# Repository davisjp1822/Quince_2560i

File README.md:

# Quince_2560i
Digital Input Protection Board with Ethernet for the Arduino Mega 2560

More information (and board available for purchase) at [https://www.three-ml.com](https://www.three-ml.com)

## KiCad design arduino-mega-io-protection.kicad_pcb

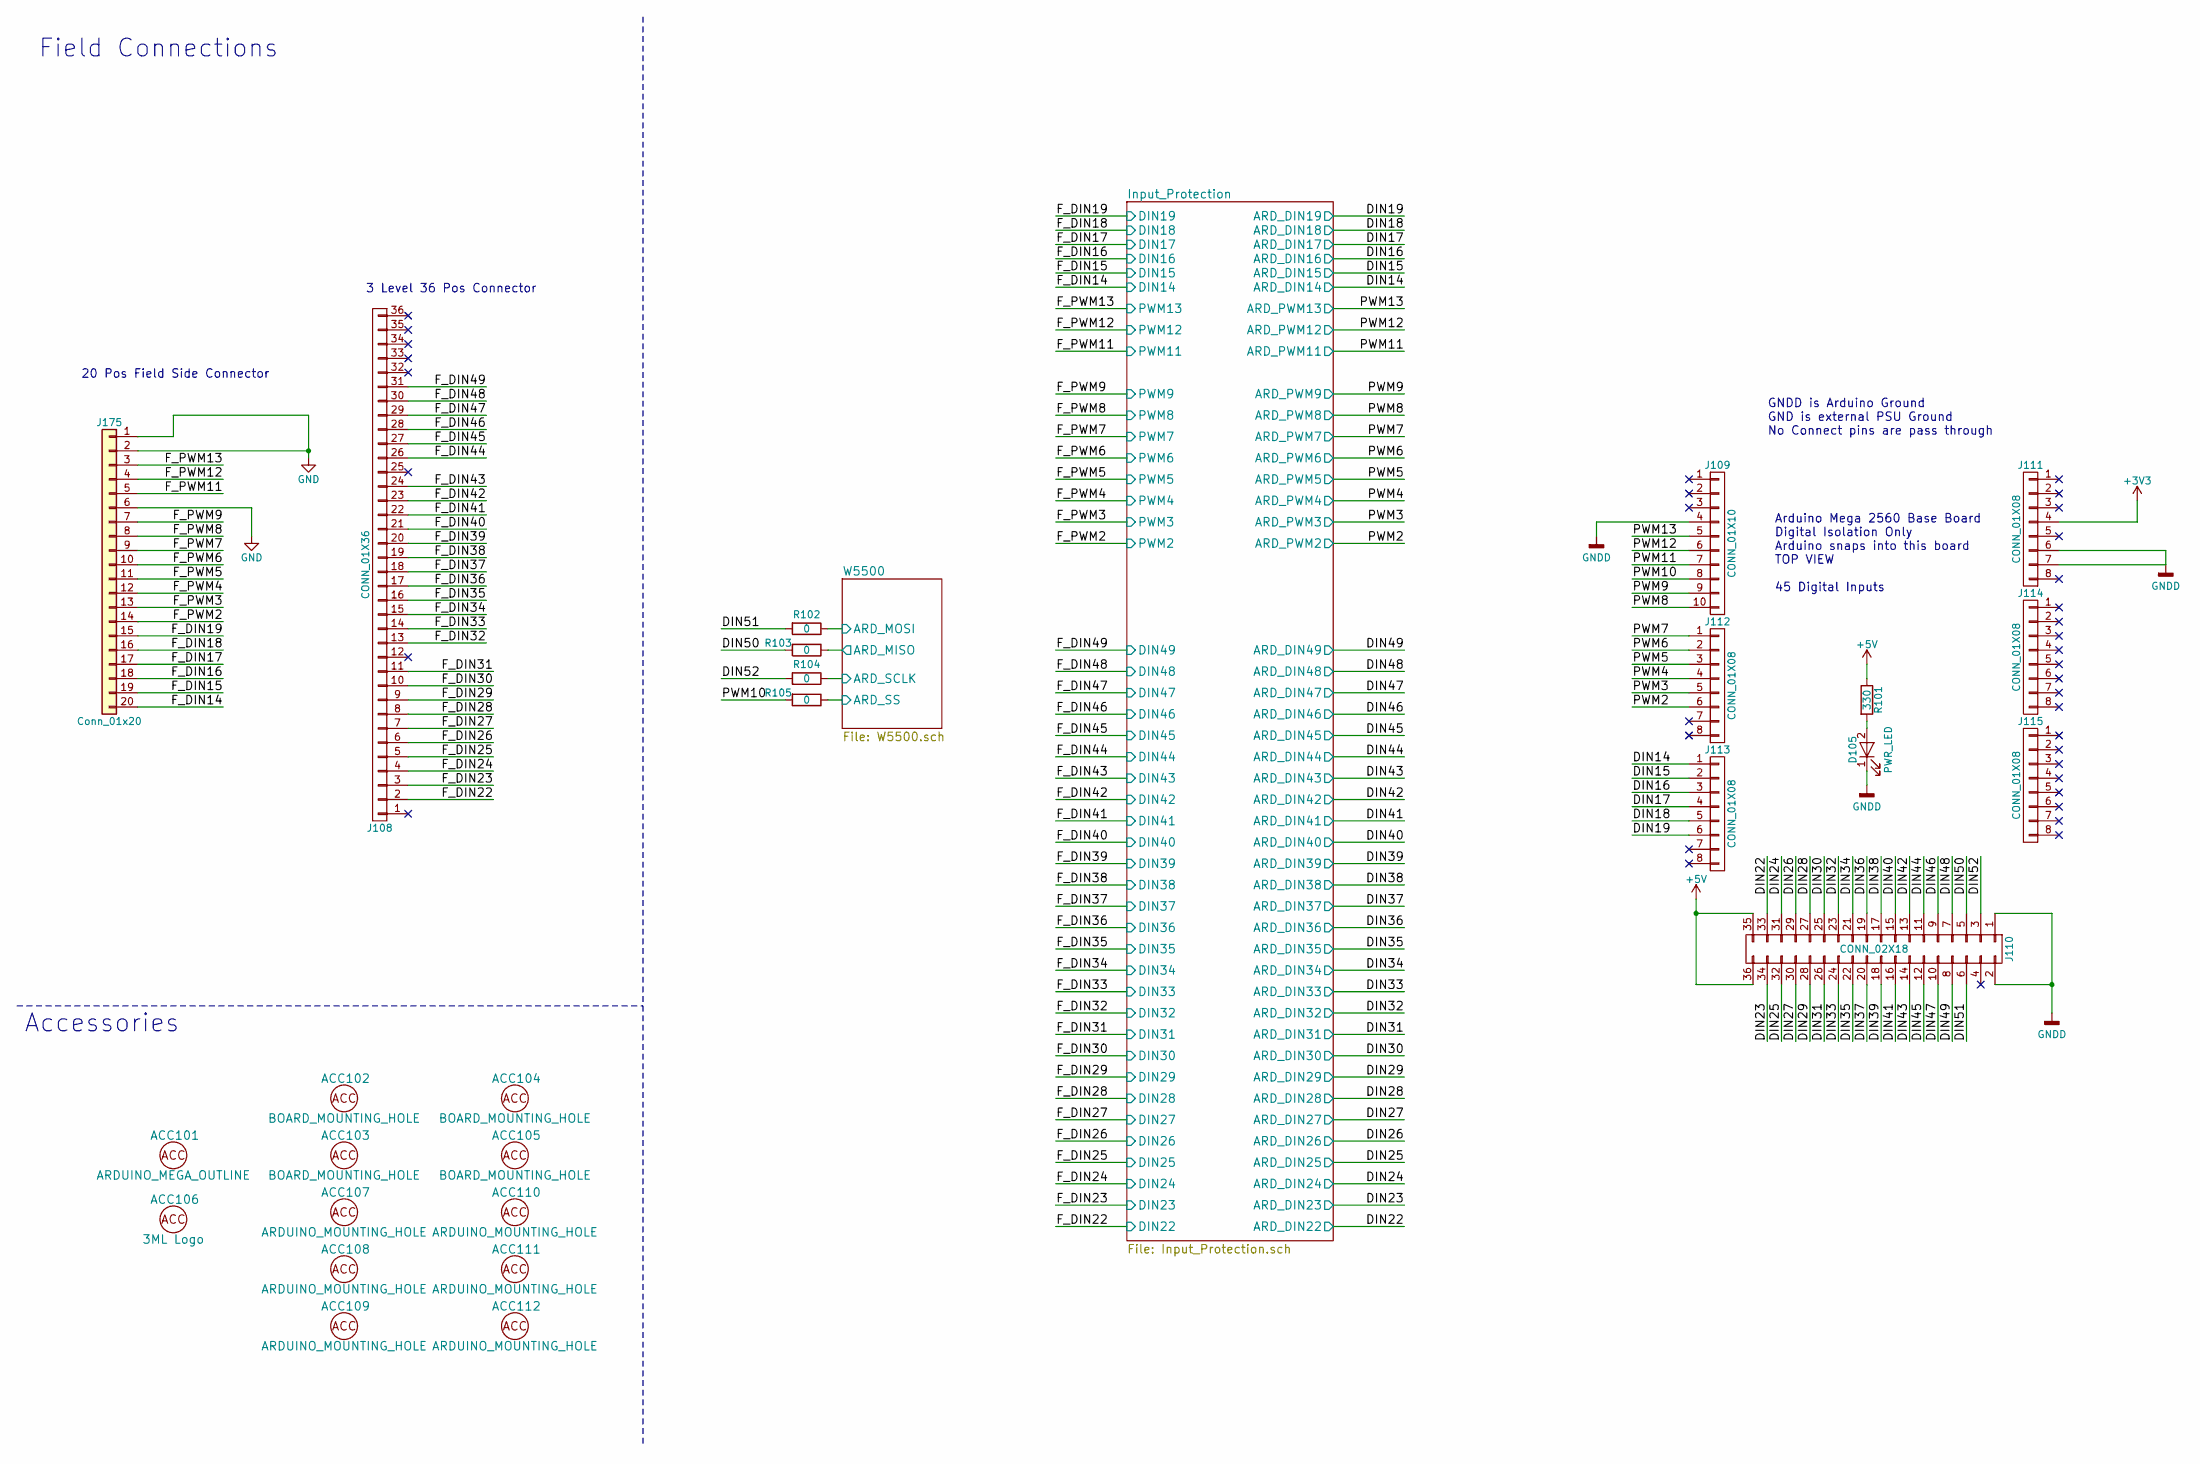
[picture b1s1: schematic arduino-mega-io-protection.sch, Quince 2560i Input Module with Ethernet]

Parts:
ACC101: ARDUINO_MEGA_OUTLINE; Arduino_Mega_2560__UPSIDE_DOWN_Footprint; MPN Value
ACC102, ACC103, ACC104, ACC105: BOARD_MOUNTING_HOLE; MountingHole_3.2mm_M3; MPN Value
ACC106: 3ML Logo; 3ML_LOGO; MPN X
ACC107, ACC108, ACC109, ACC110, ACC111, ACC112: ARDUINO_MOUNTING_HOLE; MountingHole_3.2mm_M3; MPN Value
D105: PWR_LED; LED_1206; MPN PG1101W-TR
J108: CONN_01X36; Phoenix_1727832; MPN 1727832
J109: CONN_01X10; Pin_Header_Straight_1x10_Pitch2.54mm; MPN X
J110: CONN_02X18; Pin_Header_Straight_2x18_Pitch2.54mm; MPN X
J111, J112, J113, J114, J115: CONN_01X08; Pin_Header_Straight_1x08_Pitch2.54mm; MPN X
J175: Conn_01x20; Phoenix-1x20-1709678
R101: 330; R_0805; MPN ERJ-P06J331V
R102, R103, R104, R105: 0; R_0805; MPN RC0805JR-070RL

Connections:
+3V3: J111.4; also elsewhere on the board
+5V: J110.35, J110.36, R101.1; also elsewhere on the board
/DIN14: J113.1; also elsewhere on the board
/DIN15: J113.2; also elsewhere on the board
/DIN16: J113.3; also elsewhere on the board
/DIN17: J113.4; also elsewhere on the board
/DIN18: J113.5; also elsewhere on the board
/DIN19: J113.6; also elsewhere on the board
/DIN22: J110.33; also elsewhere on the board
/DIN23: J110.34; also elsewhere on the board
/DIN24: J110.31; also elsewhere on the board
/DIN25: J110.32; also elsewhere on the board
/DIN26: J110.29; also elsewhere on the board
/DIN27: J110.30; also elsewhere on the board
/DIN28: J110.27; also elsewhere on the board
/DIN29: J110.28; also elsewhere on the board
/DIN30: J110.25; also elsewhere on the board
/DIN31: J110.26; also elsewhere on the board
/DIN32: J110.23; also elsewhere on the board
/DIN33: J110.24; also elsewhere on the board
/DIN34: J110.21; also elsewhere on the board
/DIN35: J110.22; also elsewhere on the board
/DIN36: J110.19; also elsewhere on the board
/DIN37: J110.20; also elsewhere on the board
/DIN38: J110.17; also elsewhere on the board
/DIN39: J110.18; also elsewhere on the board
/DIN40: J110.15; also elsewhere on the board
/DIN41: J110.16; also elsewhere on the board
/DIN42: J110.13; also elsewhere on the board
/DIN43: J110.14; also elsewhere on the board
/DIN44: J110.11; also elsewhere on the board
/DIN45: J110.12; also elsewhere on the board
/DIN46: J110.9; also elsewhere on the board
/DIN47: J110.10; also elsewhere on the board
/DIN48: J110.7; also elsewhere on the board
/DIN49: J110.8; also elsewhere on the board
/DIN50: J110.5, R103.2
/DIN51: J110.6, R102.2
/DIN52: J110.3, R104.2
/F_DIN14: J175.20; also elsewhere on the board
/F_DIN15: J175.19; also elsewhere on the board
/F_DIN16: J175.18; also elsewhere on the board
/F_DIN17: J175.17; also elsewhere on the board
/F_DIN18: J175.16; also elsewhere on the board
/F_DIN19: J175.15; also elsewhere on the board
/F_DIN22: J108.2; also elsewhere on the board
/F_DIN23: J108.3; also elsewhere on the board
/F_DIN24: J108.4; also elsewhere on the board
/F_DIN25: J108.5; also elsewhere on the board
/F_DIN26: J108.6; also elsewhere on the board
/F_DIN27: J108.7; also elsewhere on the board
/F_DIN28: J108.8; also elsewhere on the board
/F_DIN29: J108.9; also elsewhere on the board
/F_DIN30: J108.10; also elsewhere on the board
/F_DIN31: J108.11; also elsewhere on the board
/F_DIN32: J108.13; also elsewhere on the board
/F_DIN33: J108.14; also elsewhere on the board
/F_DIN34: J108.15; also elsewhere on the board
/F_DIN35: J108.16; also elsewhere on the board
/F_DIN36: J108.17; also elsewhere on the board
/F_DIN37: J108.18; also elsewhere on the board
/F_DIN38: J108.19; also elsewhere on the board
/F_DIN39: J108.20; also elsewhere on the board
/F_DIN40: J108.21; also elsewhere on the board
/F_DIN41: J108.22; also elsewhere on the board
/F_DIN42: J108.23; also elsewhere on the board
/F_DIN43: J108.24; also elsewhere on the board
/F_DIN44: J108.26; also elsewhere on the board
/F_DIN45: J108.27; also elsewhere on the board
/F_DIN46: J108.28; also elsewhere on the board
/F_DIN47: J108.29; also elsewhere on the board
/F_DIN48: J108.30; also elsewhere on the board
/F_DIN49: J108.31; also elsewhere on the board
/F_PWM2: J175.14; also elsewhere on the board
/F_PWM3: J175.13; also elsewhere on the board
/F_PWM4: J175.12; also elsewhere on the board
/F_PWM5: J175.11; also elsewhere on the board
/F_PWM6: J175.10; also elsewhere on the board
/F_PWM7: J175.9; also elsewhere on the board
/F_PWM8: J175.8; also elsewhere on the board
/F_PWM9: J175.7; also elsewhere on the board
/F_PWM11: J175.5; also elsewhere on the board
/F_PWM12: J175.4; also elsewhere on the board
/F_PWM13: J175.3; also elsewhere on the board
/PWM2: J112.6; also elsewhere on the board
/PWM3: J112.5; also elsewhere on the board
/PWM4: J112.4; also elsewhere on the board
/PWM5: J112.3; also elsewhere on the board
/PWM6: J112.2; also elsewhere on the board
/PWM7: J112.1; also elsewhere on the board
/PWM8: J109.10; also elsewhere on the board
/PWM9: J109.9; also elsewhere on the board
/PWM10: J109.8, R105.2
/PWM11: J109.7; also elsewhere on the board
/PWM12: J109.6; also elsewhere on the board
/PWM13: J109.5; also elsewhere on the board
/W5500/ARD_MISO: R103.1; also elsewhere on the board
/W5500/ARD_MOSI: R102.1; also elsewhere on the board
/W5500/ARD_SCLK: R104.1; also elsewhere on the board
/W5500/ARD_SS: R105.1; also elsewhere on the board
GND: J175.1, J175.2, J175.6; also elsewhere on the board
GNDD: D105.1 (K), J109.4, J110.1, J110.2, J111.6, J111.7; also elsewhere on the board
unnamed: D105.2 (A), R101.2

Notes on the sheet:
GNDD is Arduino Ground GND is external PSU Ground No Connect pins are pass through
Arduino Mega 2560 Base Board Digital Isolation Only Arduino snaps into this board TOP VIEW 45 Digital Inputs
3 Level 36 Pos Connector
20 Pos Field Side Connector
Accessories
Field Connections

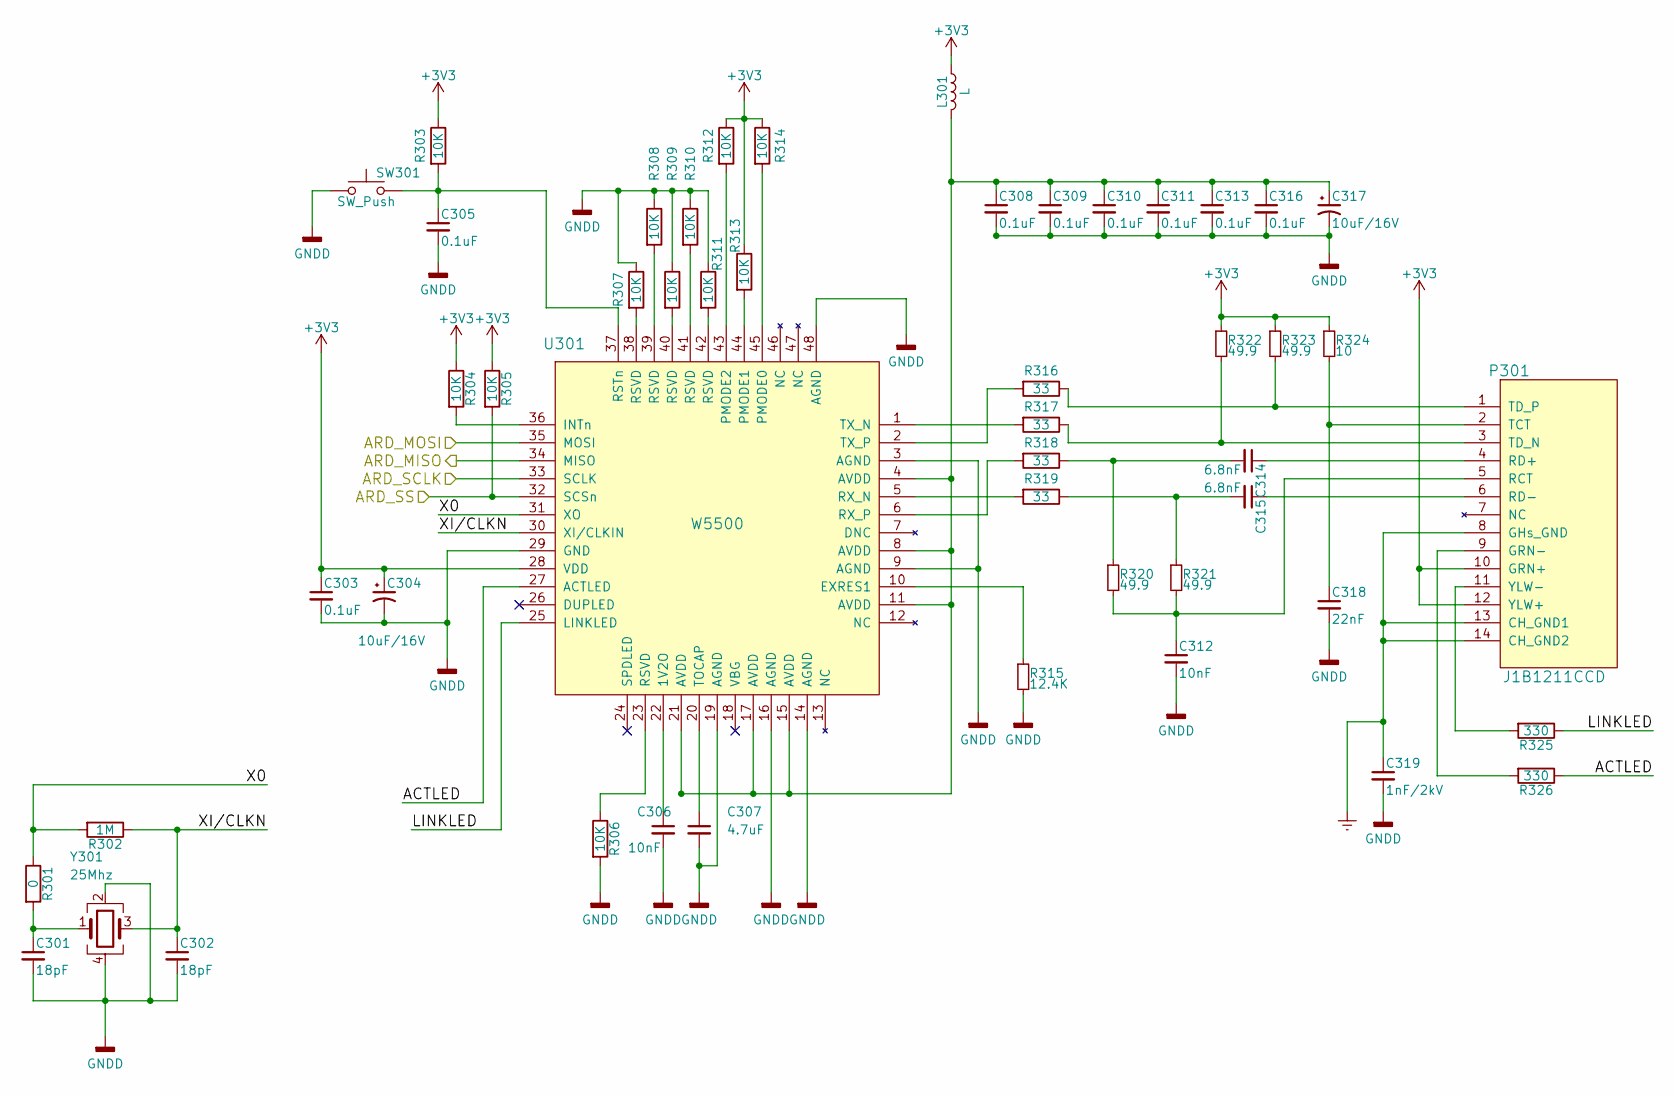
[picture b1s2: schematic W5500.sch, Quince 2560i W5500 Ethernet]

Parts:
C301, C302: 18pF; C_0603; MPN GRM1885C1H180FA01D
C303, C305, C308, C309, C310, C311, C313, C316: 0.1uF; C_0805; MPN 08055C104KAT2A
C304, C317: 10uF/16V; CP_Tantalum_Case-A_EIA-3216-18_Reflow; MPN F931C106MAA
C306, C312: 10nF; C_0805; MPN CC0805KRX7R9BB103
C307: 4.7uF; C_0805; MPN GRM21BR71C475KE51L
C314, C315: 6.8nF; C_0805; MPN CC0805KRX7R9BB682
C318: 22nF; C_0805; MPN C0805C223K5RACTU
C319: 1nF/2kV; C_1206; MPN 202R18W102KV4E
L301: L; R_1812; MPN 742792511
P301: J1B1211CCD; MPN J1B1211CCD
R301: 0; R_0805; MPN RC0805JR-070RL
R302: 1M; R_0805; MPN RC0805FR-071ML
R303, R304, R305, R306, R307, R308, R309, R310, R311, R312, R313, R314: 10K; R_0805; MPN RC0805JR-0710KL
R315: 12.4K; R_0805; MPN RC0805FR-0712K4L
R316, R317, R318, R319: 33; R_0805; MPN RC0805FR-0733RL
R320, R321, R322, R323: 49.9; R_0805; MPN RC0805FR-0749R9L
R324: 10; R_0805; MPN RC0805FR-0710RL
R325, R326: 330; R_0805; MPN RMCF0805JT330R
SW301: SW_Push; SW_SPST_PTS645; MPN PTS645SK43SMTR92 LFS
U301: W5500; LQFP-48_7x7mm_Pitch0.5mm; MPN W5500
Y301: 25Mhz; Oscillator_SMD_Abracon_ASE-4pin_3.2x2.5mm; MPN ABM8G-25.000MHZ-18-D2Y-T

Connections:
+3V3: C303.1, C304.1, L301.1, P301.10 (GRN+), P301.12 (YLW+), R303.1, R304.1, R305.1, R312.1, R313.1, R314.1, R322.1, R323.1, R324.1, U301.28 (VDD); also elsewhere on the board
/W5500/ACTLED: R326.1, U301.27 (ACTLED)
/W5500/ARD_MISO: U301.34 (MISO); also elsewhere on the board
/W5500/ARD_MOSI: U301.35 (MOSI); also elsewhere on the board
/W5500/ARD_SCLK: U301.33 (SCLK); also elsewhere on the board
/W5500/ARD_SS: R305.2, U301.32 (SCSn); also elsewhere on the board
/W5500/LINKLED: R325.1, U301.25 (LINKLED)
/W5500/X0: R301.1, R302.2, U301.31 (XO)
/W5500/XI/CLKN: C302.1, R302.1, U301.30 (XI/CLKIN), Y301.3
Earth: C319.1, P301.8 (GHs_GND), P301.13 (CH_GND1), P301.14 (CH_GND2)
GNDD: C301.2, C302.2, C303.2, C304.2, C305.2, C306.2, C307.2, C308.2, C309.2, C310.2, C311.2, C312.2, C313.2, C316.2, C317.2, C318.2, C319.2, R306.2, R307.1, R308.1, R309.1, R310.1, R311.1, R315.2, SW301.1, U301.3 (AGND), U301.9 (AGND), U301.14 (AGND), U301.16 (AGND), U301.19 (AGND), U301.29 (GND), U301.48 (AGND), Y301.2, Y301.4; also elsewhere on the board
unnamed: C301.1, R301.2, Y301.1
unnamed: C305.1, R303.2, SW301.2, U301.37 (RSTn)
unnamed: C306.1, U301.22 (1V2O)
unnamed: C307.1, U301.20 (TOCAP)
unnamed: C308.1, C309.1, C310.1, C311.1, C313.1, C316.1, C317.1, L301.2, U301.4 (AVDD), U301.8 (AVDD), U301.11 (AVDD), U301.15 (AVDD), U301.17 (AVDD), U301.21 (AVDD)
unnamed: C312.1, P301.5 (RCT), R320.2, R321.2
unnamed: C314.1, P301.4 (RD+)
unnamed: C314.2, R318.1, R320.1
unnamed: C315.1, P301.6 (RD-)
unnamed: C315.2, R319.1, R321.1
unnamed: C318.1, P301.2 (TCT), R324.2
unnamed: P301.1 (TD_P), R316.1, R323.2
unnamed: P301.3 (TD_N), R317.1, R322.2
unnamed: P301.9 (GRN-), R326.2
unnamed: P301.11 (YLW-), R325.2
unnamed: R304.2, U301.36 (INTn)
unnamed: R306.1, U301.23 (RSVD)
unnamed: R307.2, U301.38 (RSVD)
unnamed: R308.2, U301.39 (RSVD)
unnamed: R309.2, U301.40 (RSVD)
unnamed: R310.2, U301.41 (RSVD)
unnamed: R311.2, U301.42 (RSVD)
unnamed: R312.2, U301.43 (PMODE2)
unnamed: R313.2, U301.44 (PMODE1)
unnamed: R314.2, U301.45 (PMODE0)
unnamed: R315.1, U301.10 (EXRES1)
unnamed: R316.2, U301.2 (TX_P)
unnamed: R317.2, U301.1 (TX_N)
unnamed: R318.2, U301.6 (RX_P)
unnamed: R319.2, U301.5 (RX_N)

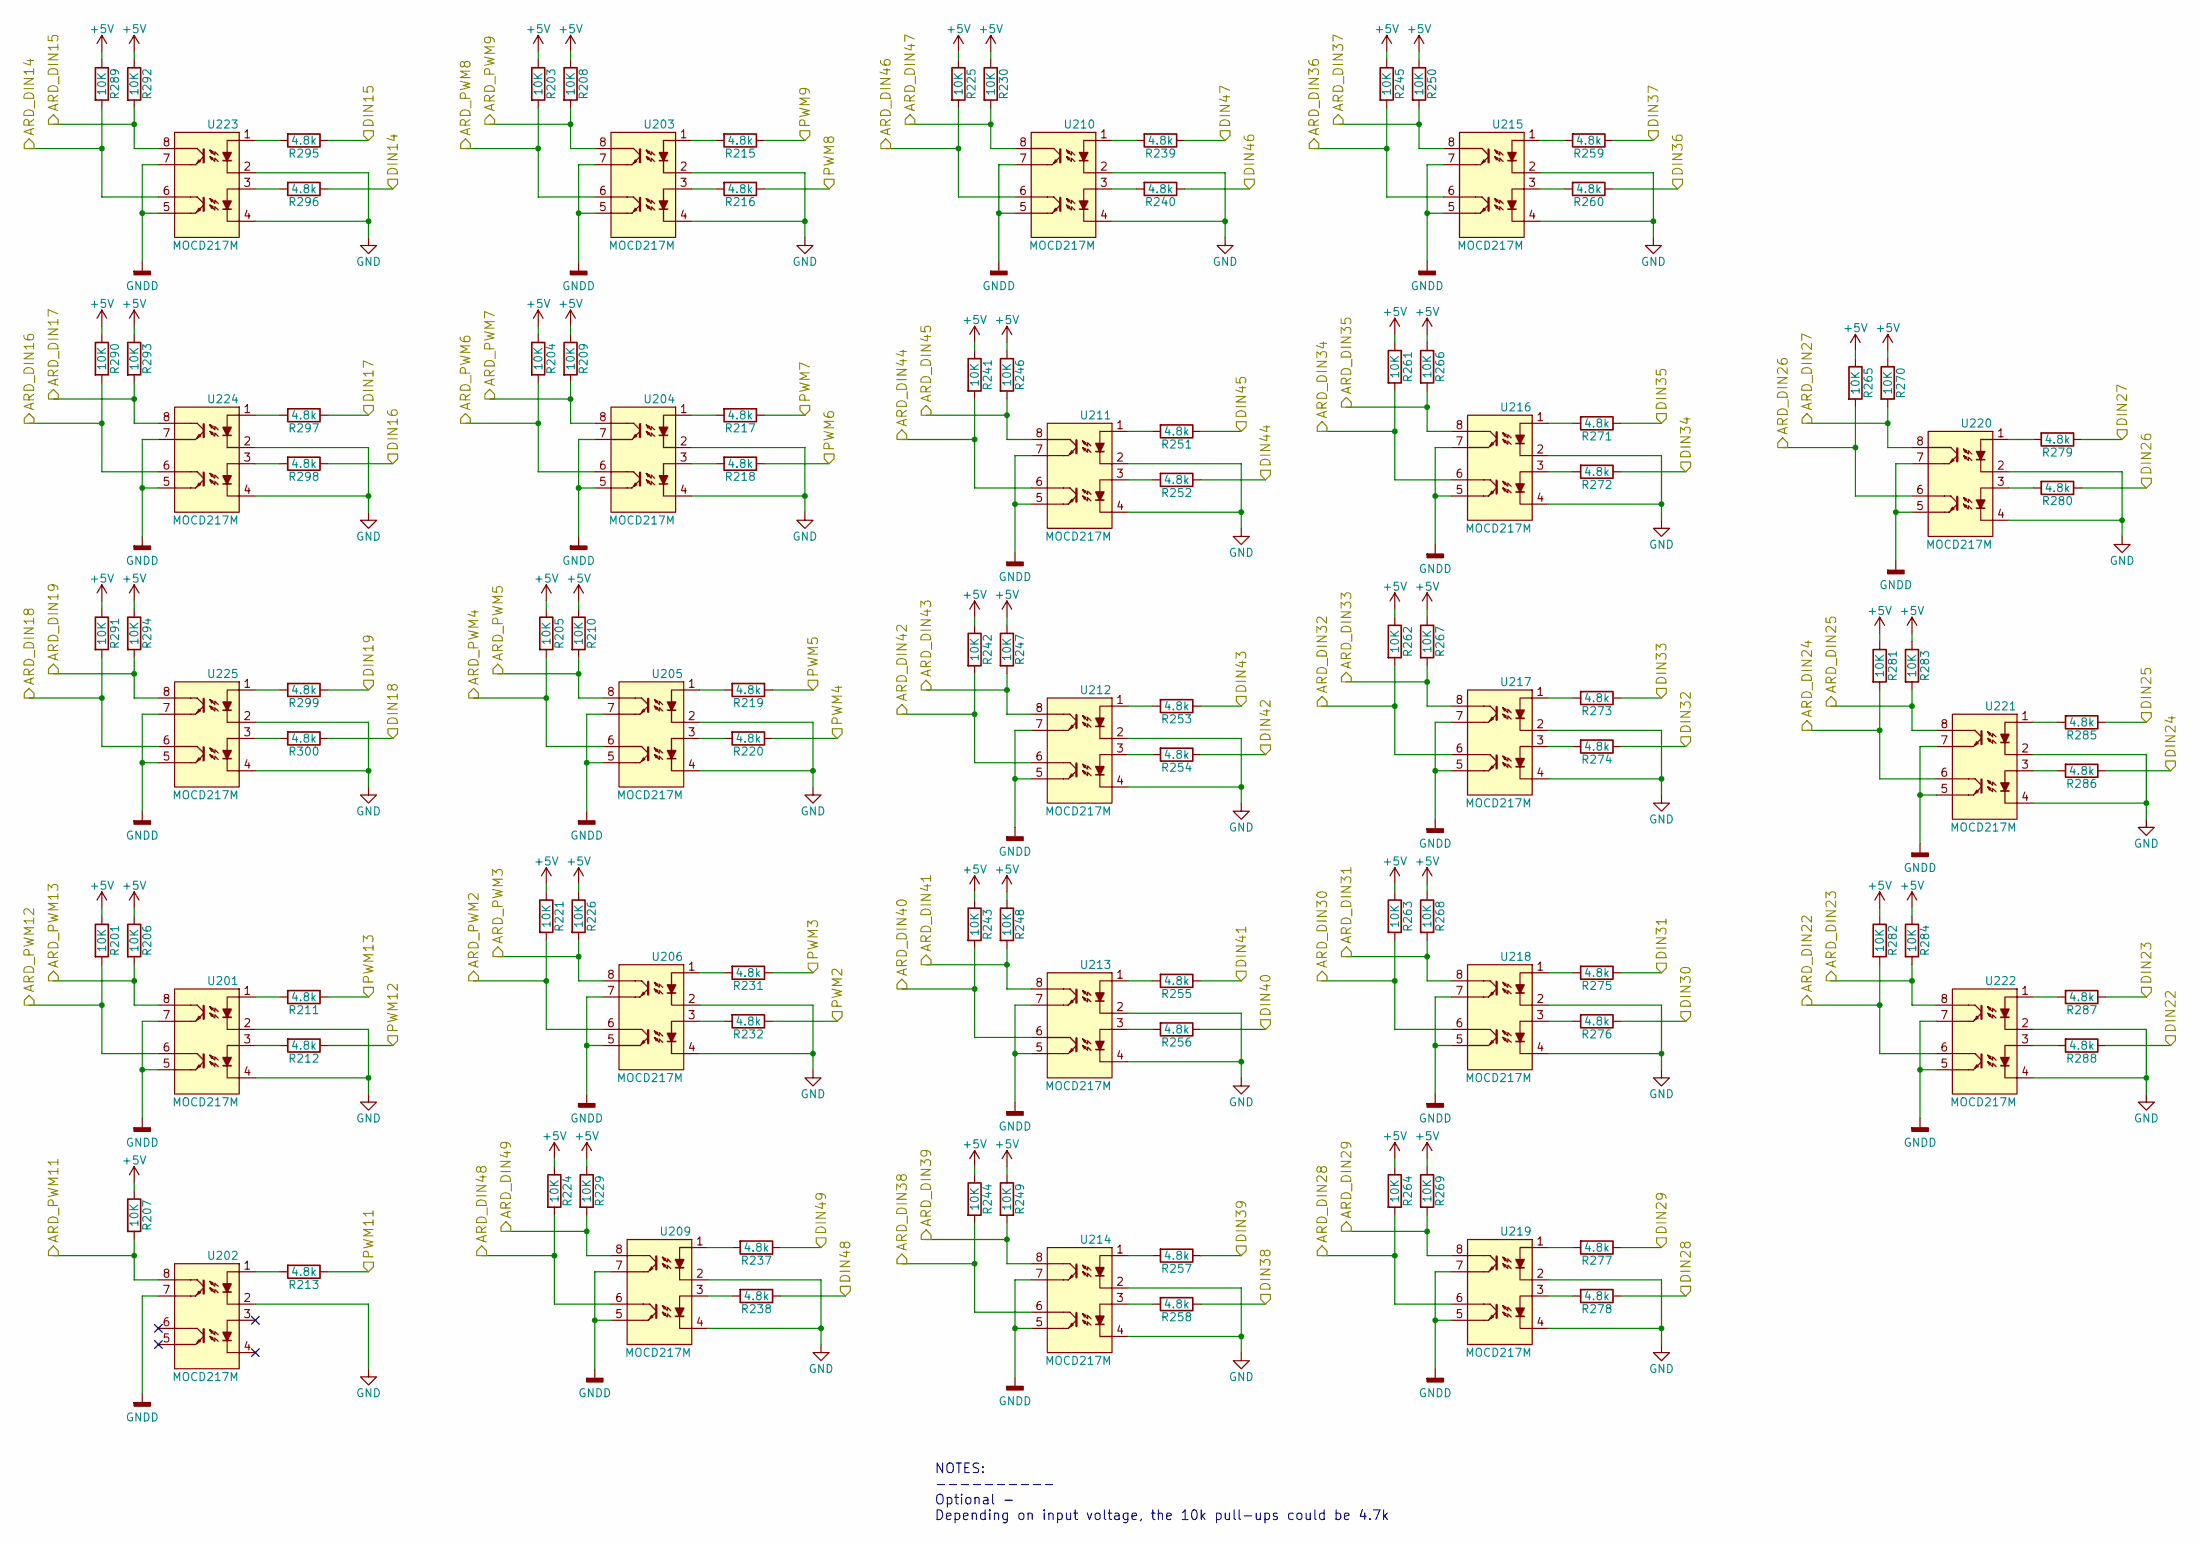
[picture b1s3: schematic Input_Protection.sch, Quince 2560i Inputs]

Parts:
R201, R203, R204, R205, R206, R207, R208, R209, R210, R221, R224, R225, R226, R229, R230, R241, R242, R243, R244, R245, R246, R247, R248, R249, R250, R261, R262, R263, R264, R265, R266, R267, R268, R269, R270, R281, R282, R283, R284, R289, R290, R291, R292, R293, R294: 10K; R_0805; MPN RC0805JR-0710KL
R211, R212, R213, R215, R216, R217, R218, R219, R220, R231, R232, R237, R238, R239, R240, R251, R252, R253, R254, R255, R256, R257, R258, R259, R260, R271, R272, R273, R274, R275, R276, R277, R278, R279, R280, R285, R286, R287, R288, R295, R296, R297, R298, R299, R300: 4.8k; R_1206; MPN RNCP1206FTD4K75
U201, U202, U203, U204, U205, U206, U209, U210, U211, U212, U213, U214, U215, U216, U217, U218, U219, U220, U221, U222, U223, U224, U225: MOCD217M; SOIC-8_3.9x4.9mm_Pitch1.27mm; MPN MOCD217M

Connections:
+5V: R201.1, R203.1, R204.1, R205.1, R206.1, R207.1, R208.1, R209.1, R210.1, R221.1, R224.1, R225.1, R226.1, R229.1, R230.1, R241.1, R242.1, R243.1, R244.1, R245.1, R246.1, R247.1, R248.1, R249.1, R250.1, R261.1, R262.1, R263.1, R264.1, R265.1, R266.1, R267.1, R268.1, R269.1, R270.1, R281.1, R282.1, R283.1, R284.1, R289.1, R290.1, R291.1, R292.1, R293.1, R294.1; also elsewhere on the board
/DIN14: R289.2, U223.6; also elsewhere on the board
/DIN15: R292.2, U223.8; also elsewhere on the board
/DIN16: R290.2, U224.6; also elsewhere on the board
/DIN17: R293.2, U224.8; also elsewhere on the board
/DIN18: R291.2, U225.6; also elsewhere on the board
/DIN19: R294.2, U225.8; also elsewhere on the board
/DIN22: R282.2, U222.6; also elsewhere on the board
/DIN23: R284.2, U222.8; also elsewhere on the board
/DIN24: R281.2, U221.6; also elsewhere on the board
/DIN25: R283.2, U221.8; also elsewhere on the board
/DIN26: R265.2, U220.6; also elsewhere on the board
/DIN27: R270.2, U220.8; also elsewhere on the board
/DIN28: R264.2, U219.6; also elsewhere on the board
/DIN29: R269.2, U219.8; also elsewhere on the board
/DIN30: R263.2, U218.6; also elsewhere on the board
/DIN31: R268.2, U218.8; also elsewhere on the board
/DIN32: R262.2, U217.6; also elsewhere on the board
/DIN33: R267.2, U217.8; also elsewhere on the board
/DIN34: R261.2, U216.6; also elsewhere on the board
/DIN35: R266.2, U216.8; also elsewhere on the board
/DIN36: R245.2, U215.6; also elsewhere on the board
/DIN37: R250.2, U215.8; also elsewhere on the board
/DIN38: R244.2, U214.6; also elsewhere on the board
/DIN39: R249.2, U214.8; also elsewhere on the board
/DIN40: R243.2, U213.6; also elsewhere on the board
/DIN41: R248.2, U213.8; also elsewhere on the board
/DIN42: R242.2, U212.6; also elsewhere on the board
/DIN43: R247.2, U212.8; also elsewhere on the board
/DIN44: R241.2, U211.6; also elsewhere on the board
/DIN45: R246.2, U211.8; also elsewhere on the board
/DIN46: R225.2, U210.6; also elsewhere on the board
/DIN47: R230.2, U210.8; also elsewhere on the board
/DIN48: R224.2, U209.6; also elsewhere on the board
/DIN49: R229.2, U209.8; also elsewhere on the board
/F_DIN14: R296.1; also elsewhere on the board
/F_DIN15: R295.1; also elsewhere on the board
/F_DIN16: R298.1; also elsewhere on the board
/F_DIN17: R297.1; also elsewhere on the board
/F_DIN18: R300.1; also elsewhere on the board
/F_DIN19: R299.1; also elsewhere on the board
/F_DIN22: R288.1; also elsewhere on the board
/F_DIN23: R287.1; also elsewhere on the board
/F_DIN24: R286.1; also elsewhere on the board
/F_DIN25: R285.1; also elsewhere on the board
/F_DIN26: R280.1; also elsewhere on the board
/F_DIN27: R279.1; also elsewhere on the board
/F_DIN28: R278.1; also elsewhere on the board
/F_DIN29: R277.1; also elsewhere on the board
/F_DIN30: R276.1; also elsewhere on the board
/F_DIN31: R275.1; also elsewhere on the board
/F_DIN32: R274.1; also elsewhere on the board
/F_DIN33: R273.1; also elsewhere on the board
/F_DIN34: R272.1; also elsewhere on the board
/F_DIN35: R271.1; also elsewhere on the board
/F_DIN36: R260.1; also elsewhere on the board
/F_DIN37: R259.1; also elsewhere on the board
/F_DIN38: R258.1; also elsewhere on the board
/F_DIN39: R257.1; also elsewhere on the board
/F_DIN40: R256.1; also elsewhere on the board
/F_DIN41: R255.1; also elsewhere on the board
/F_DIN42: R254.1; also elsewhere on the board
/F_DIN43: R253.1; also elsewhere on the board
/F_DIN44: R252.1; also elsewhere on the board
/F_DIN45: R251.1; also elsewhere on the board
/F_DIN46: R240.1; also elsewhere on the board
/F_DIN47: R239.1; also elsewhere on the board
/F_DIN48: R238.1; also elsewhere on the board
/F_DIN49: R237.1; also elsewhere on the board
/F_PWM2: R232.1; also elsewhere on the board
/F_PWM3: R231.1; also elsewhere on the board
/F_PWM4: R220.1; also elsewhere on the board
/F_PWM5: R219.1; also elsewhere on the board
/F_PWM6: R218.1; also elsewhere on the board
/F_PWM7: R217.1; also elsewhere on the board
/F_PWM8: R216.1; also elsewhere on the board
/F_PWM9: R215.1; also elsewhere on the board
/F_PWM11: R213.1; also elsewhere on the board
/F_PWM12: R212.1; also elsewhere on the board
/F_PWM13: R211.1; also elsewhere on the board
/PWM2: R221.2, U206.6; also elsewhere on the board
/PWM3: R226.2, U206.8; also elsewhere on the board
/PWM4: R205.2, U205.6; also elsewhere on the board
/PWM5: R210.2, U205.8; also elsewhere on the board
/PWM6: R204.2, U204.6; also elsewhere on the board
/PWM7: R209.2, U204.8; also elsewhere on the board
/PWM8: R203.2, U203.6; also elsewhere on the board
/PWM9: R208.2, U203.8; also elsewhere on the board
/PWM11: R207.2, U202.8; also elsewhere on the board
/PWM12: R201.2, U201.6; also elsewhere on the board
/PWM13: R206.2, U201.8; also elsewhere on the board
GND: U201.2, U201.4, U202.2, U203.2, U203.4, U204.2, U204.4, U205.2, U205.4, U206.2, U206.4, U209.2, U209.4, U210.2, U210.4, U211.2, U211.4, U212.2, U212.4, U213.2, U213.4, U214.2, U214.4, U215.2, U215.4, U216.2, U216.4, U217.2, U217.4, U218.2, U218.4, U219.2, U219.4, U220.2, U220.4, U221.2, U221.4, U222.2, U222.4, U223.2, U223.4, U224.2, U224.4, U225.2, U225.4; also elsewhere on the board
GNDD: U201.5, U201.7, U202.7, U203.5, U203.7, U204.5, U204.7, U205.5, U205.7, U206.5, U206.7, U209.5, U209.7, U210.5, U210.7, U211.5, U211.7, U212.5, U212.7, U213.5, U213.7, U214.5, U214.7, U215.5, U215.7, U216.5, U216.7, U217.5, U217.7, U218.5, U218.7, U219.5, U219.7, U220.5, U220.7, U221.5, U221.7, U222.5, U222.7, U223.5, U223.7, U224.5, U224.7, U225.5, U225.7; also elsewhere on the board
unnamed: R211.2, U201.1
unnamed: R212.2, U201.3
unnamed: R213.2, U202.1
unnamed: R215.2, U203.1
unnamed: R216.2, U203.3
unnamed: R217.2, U204.1
unnamed: R218.2, U204.3
unnamed: R219.2, U205.1
unnamed: R220.2, U205.3
unnamed: R231.2, U206.1
unnamed: R232.2, U206.3
unnamed: R237.2, U209.1
unnamed: R238.2, U209.3
unnamed: R239.2, U210.1
unnamed: R240.2, U210.3
unnamed: R251.2, U211.1
unnamed: R252.2, U211.3
unnamed: R253.2, U212.1
unnamed: R254.2, U212.3
unnamed: R255.2, U213.1
unnamed: R256.2, U213.3
unnamed: R257.2, U214.1
unnamed: R258.2, U214.3
unnamed: R259.2, U215.1
unnamed: R260.2, U215.3
unnamed: R271.2, U216.1
unnamed: R272.2, U216.3
unnamed: R273.2, U217.1
unnamed: R274.2, U217.3
unnamed: R275.2, U218.1
unnamed: R276.2, U218.3
unnamed: R277.2, U219.1
unnamed: R278.2, U219.3
unnamed: R279.2, U220.1
unnamed: R280.2, U220.3
unnamed: R285.2, U221.1
unnamed: R286.2, U221.3
unnamed: R287.2, U222.1
unnamed: R288.2, U222.3
unnamed: R295.2, U223.1
unnamed: R296.2, U223.3
unnamed: R297.2, U224.1
unnamed: R298.2, U224.3
unnamed: R299.2, U225.1
unnamed: R300.2, U225.3

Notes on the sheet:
NOTES: ---------- Optional - Depending on input voltage, the 10k pull-ups could be 4.7k

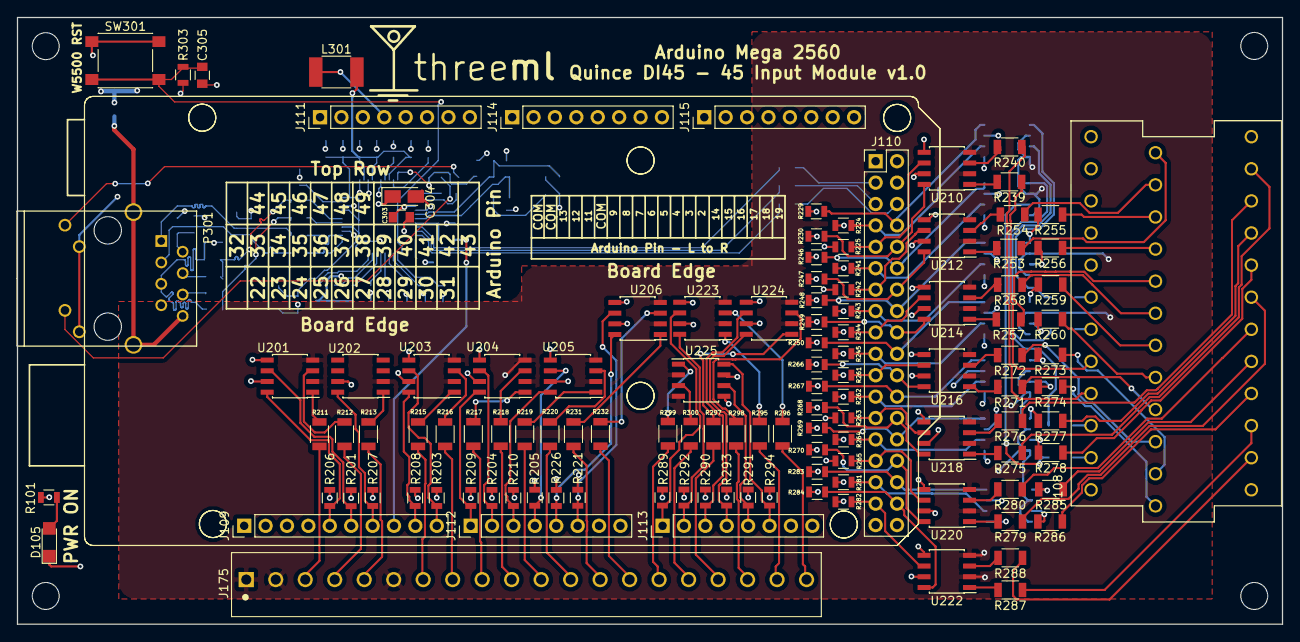
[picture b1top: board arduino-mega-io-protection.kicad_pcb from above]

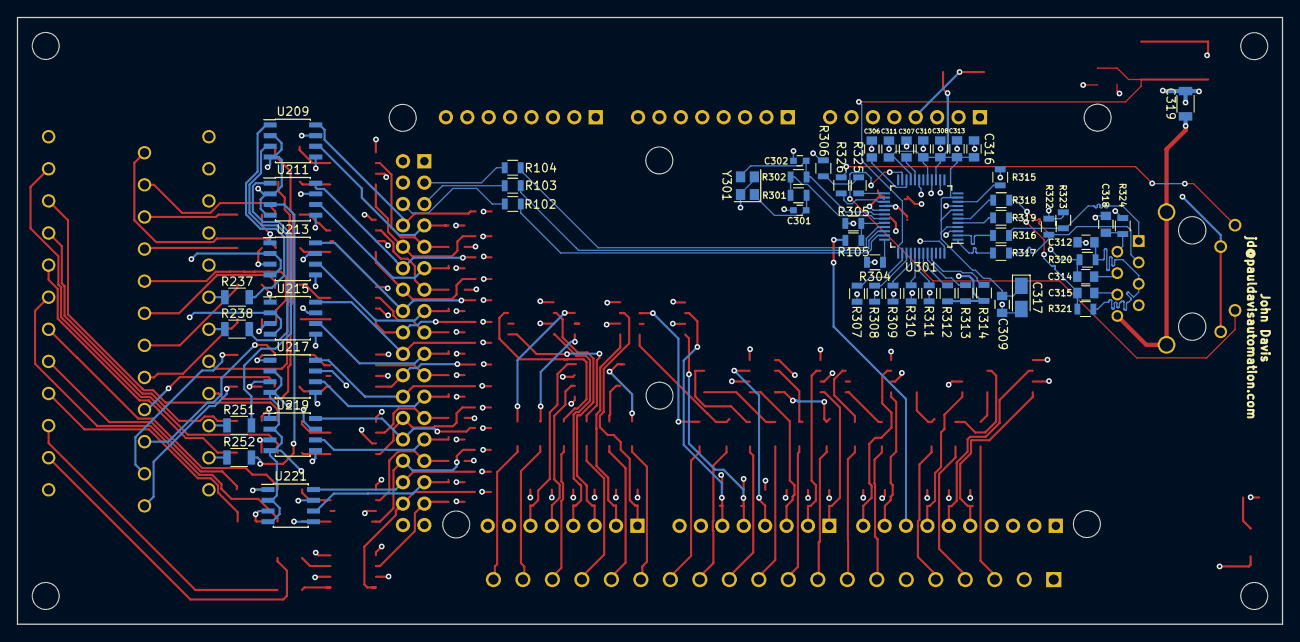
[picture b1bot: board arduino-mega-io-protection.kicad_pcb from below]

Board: 4 copper layers, 150.1 x 72.0 mm, 191 parts (58 on the bottom side), 183 nets.

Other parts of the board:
ACC101#2: ARDUINO_MEGA_OUTLINE; Arduino_Mega_2560__UPSIDE_DOWN_Footprint

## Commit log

2017-04-27 footprints cleaned-up and submitted to oshpark!
2017-05-10 inserting part information for connectors into BOM
2017-06-04 adding serial 1, 2, and 3 as protected inputs
2017-06-05 moving schematics around making room for ethernet stuff
2017-06-07 W5500 schematic complete and populated
2017-06-07 connecting spi lines and cleaning-up I/O
2017-06-08 more work on ethernet layout
2017-06-12 more tweaks
2017-06-16 almost final design - just need to add protection diodes
2017-06-21 final design sent to fab
2017-07-13 fixing BOM for arduino connectors and updating some other items
2017-08-07 getting ready to add master component library
2017-08-09 adding global hardware library, also fixed some footprint issues and added reverse protection diodes. also cleaned-up design
2017-08-09 updating submodule
2017-08-12 updated for rev2 to go to OSHPark. Fixed footprints and changed topside routing to have better noise characteristics
2017-08-12 updating solder mask to reflect product name - sent to OSHPark
2017-08-25 fixing some component/BOM part numbers
2017-09-13 moving diodes away from edge
2017-09-16 fixing diode location
2017-09-16 updating schematic to look more consistent
2017-09-16 updating schematic and library to use a Phoenix header for the 1x20
2017-09-16 fixing title block and page size
2017-09-17 removing unnecessary diodes
2017-09-17 fixing footprint issue with oscillator (missing paste)
2018-06-11 adding arduino sample code
